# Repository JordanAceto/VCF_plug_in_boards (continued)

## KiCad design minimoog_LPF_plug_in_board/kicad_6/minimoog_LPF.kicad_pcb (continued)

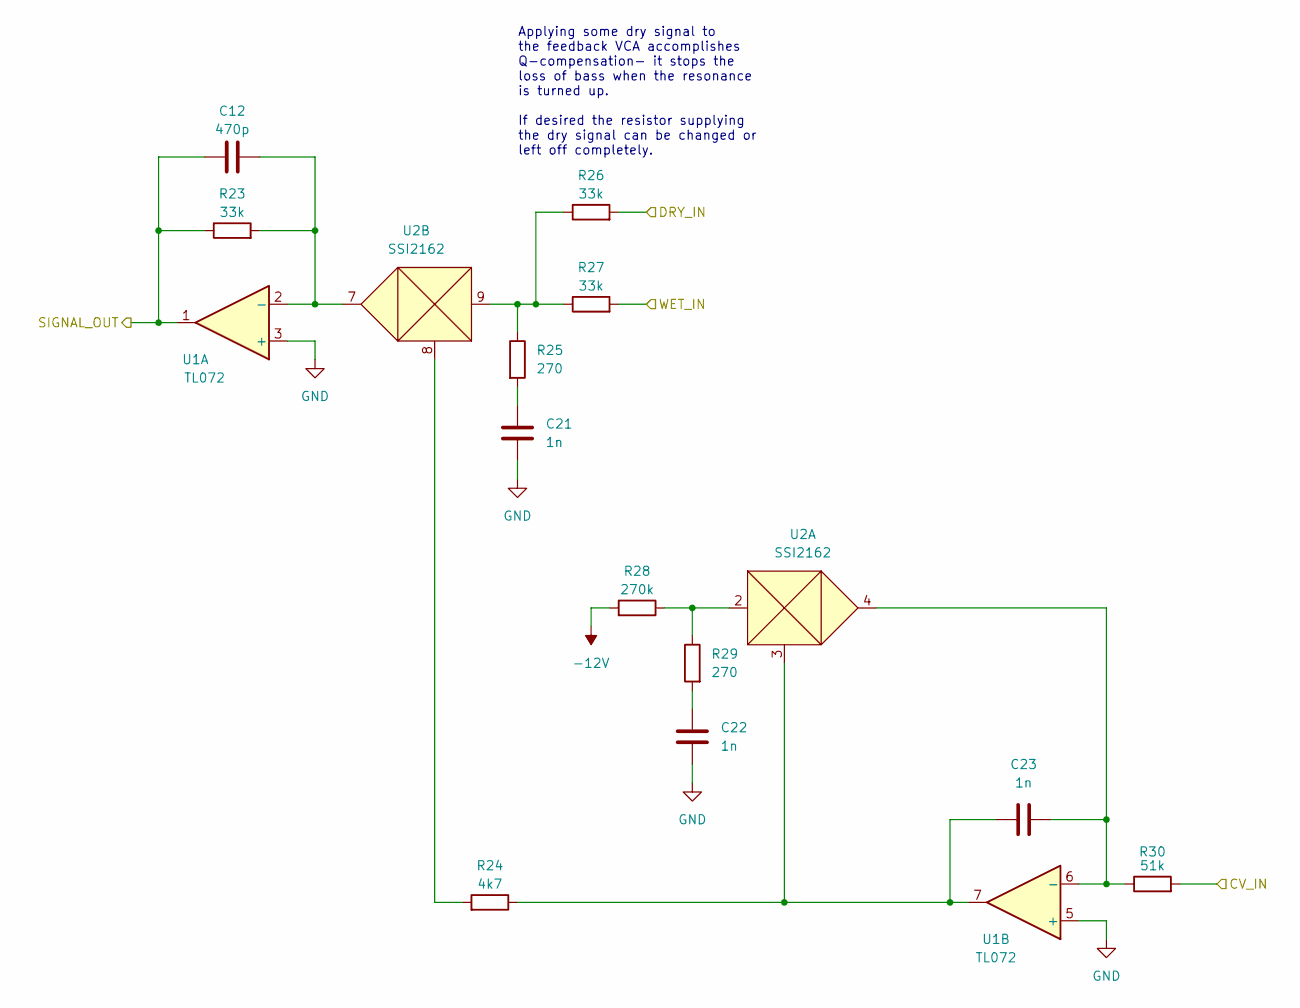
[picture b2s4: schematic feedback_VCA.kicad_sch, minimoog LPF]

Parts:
C12: 470p; C_0603_1608Metric
C21, C22, C23: 1n; C_0603_1608Metric
R23, R26, R27: 33k; R_0603_1608Metric
R24: 4k7; R_0603_1608Metric
R25, R29: 270; R_0603_1608Metric
R28: 270k; R_0603_1608Metric
R30: 51k; R_0603_1608Metric
U1: TL072; SOIC-8_3.9x4.9mm_P1.27mm
U2: SSI2162; SSOP-10_3.9x4.9mm_P1.00mm

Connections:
-12V: R28.2; also elsewhere on the board
/DRY_SIGNAL: R26.2; also elsewhere on the board
/feedback_VCA/CV_IN: R30.2; also elsewhere on the board
/feedback_VCA/SIGNAL_OUT: C12.1, R23.1, U1.1; also elsewhere on the board
/feedback_VCA/WET_IN: R27.2; also elsewhere on the board
GND: C21.2, C22.2, U1.3 (+), U1.5 (+); also elsewhere on the board
unnamed: C12.2, R23.2, U1.2 (-), U2.7
unnamed: C21.1, R25.2
unnamed: C22.1, R29.2
unnamed: C23.1, R24.1, U1.7, U2.3
unnamed: C23.2, R30.1, U1.6 (-), U2.4
unnamed: R24.2, U2.8
unnamed: R25.1, R26.1, R27.1, U2.9
unnamed: R28.1, R29.1, U2.2

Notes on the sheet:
Applying some dry signal to the feedback VCA accomplishes Q-compensation- it stops the loss of bass when the resonance is turned up. If desired the resistor supplying the dry signal can be changed or left off completely.

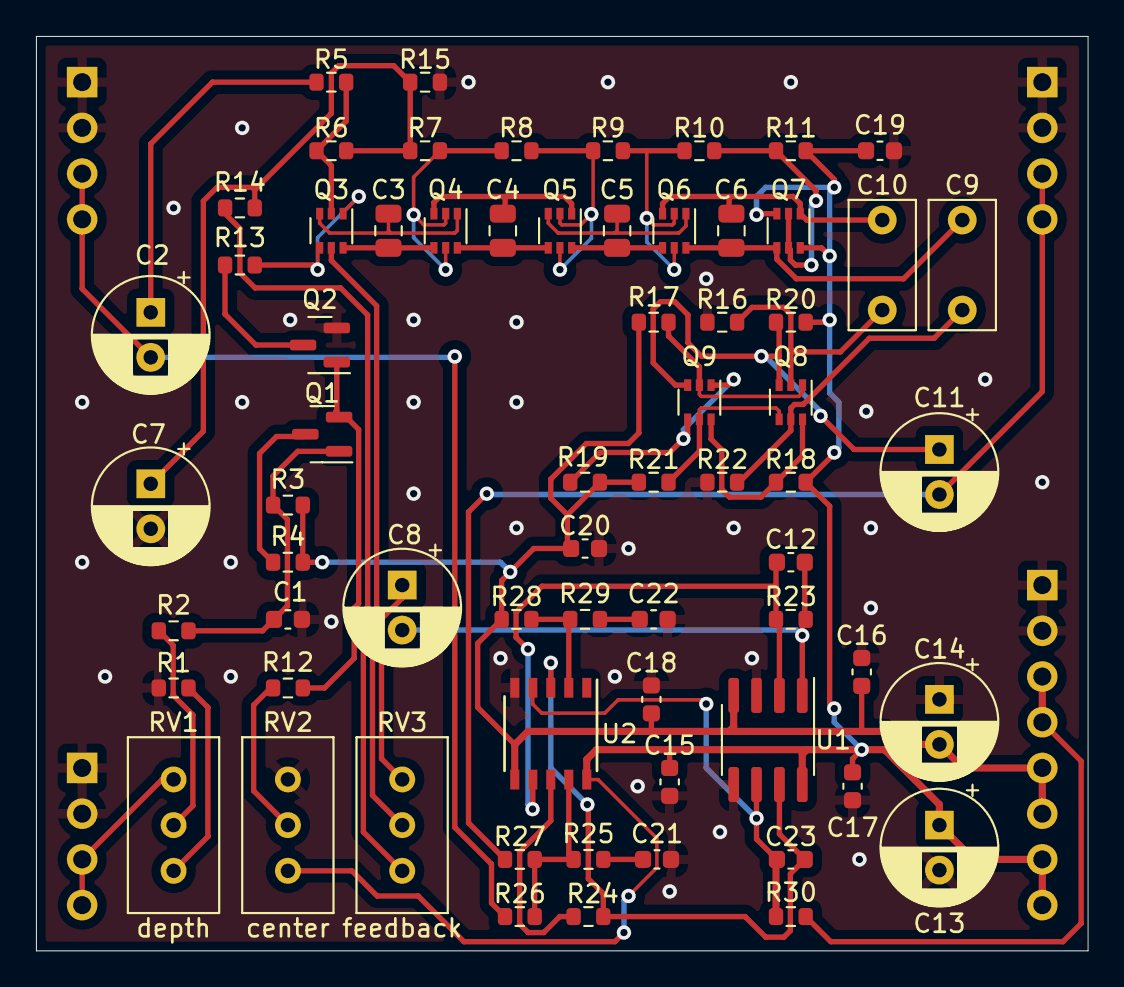
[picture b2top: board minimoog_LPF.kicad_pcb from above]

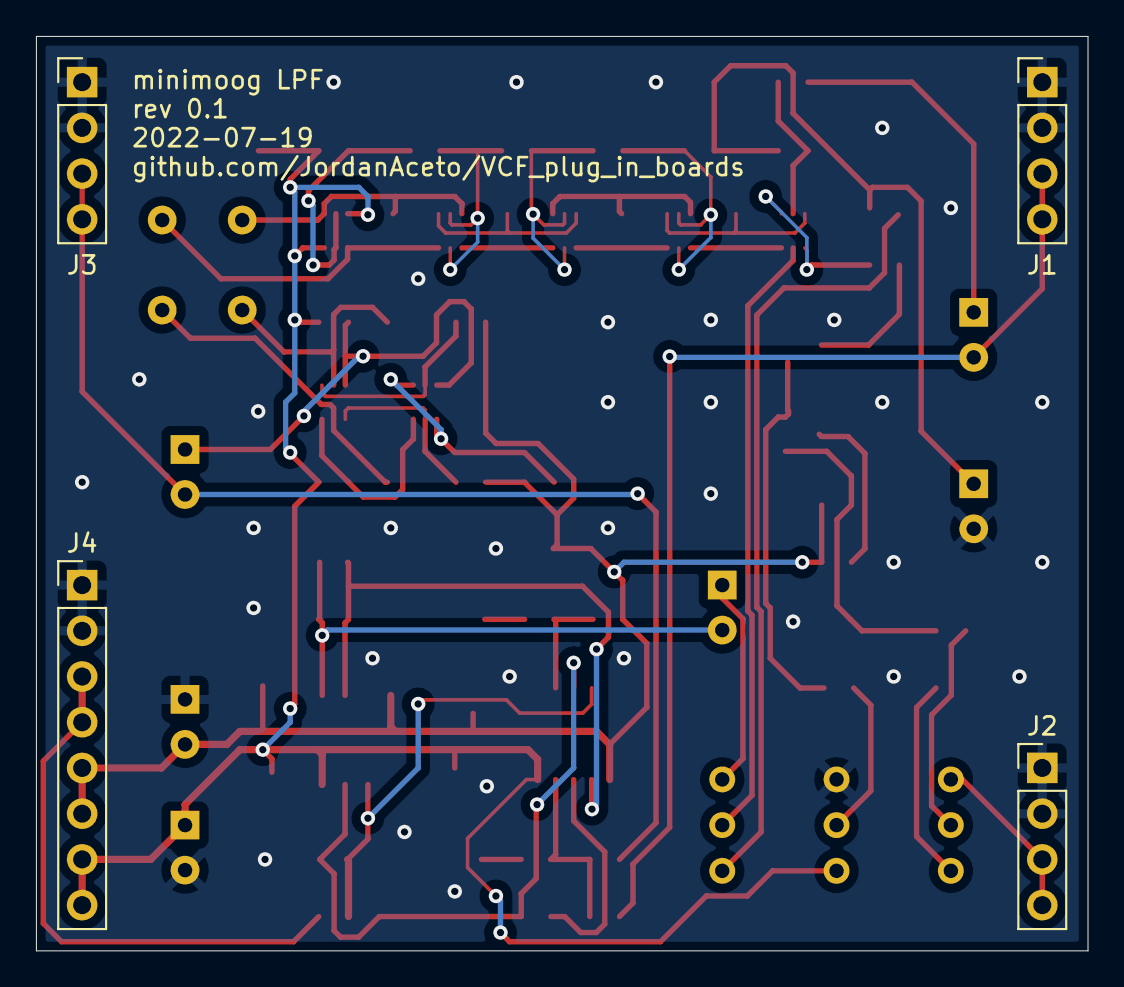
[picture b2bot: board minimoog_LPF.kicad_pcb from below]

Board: 2 copper layers, 58.4 x 50.8 mm, 71 parts (4 on the bottom side), 49 nets.

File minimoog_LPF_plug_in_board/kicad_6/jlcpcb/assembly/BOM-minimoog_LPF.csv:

Comment,Designator,Footprint,LCSC
100nF,"C15,C16,C17,C18,C19,C20",C_0603_1608Metric,C14663
100p,C12,C_0603_1608Metric,C14858
1n,"C1,C21,C22,C23",C_0603_1608Metric,C1588
MMBT3904,Q2,SOT-23,C20526
1k,R2,R_0603_1608Metric,C21190
1k2,"R18,R19,R20",R_0603_1608Metric,C22765
150,"R10,R7,R8,R9",R_0603_1608Metric,C22808
220k,"R17,R21,R3",R_0603_1608Metric,C22961
220,"R1,R11,R15",R_0603_1608Metric,C22962
270k,R28,R_0603_1608Metric,C22965
270,"R25,R29",R_0603_1608Metric,C22966
330,"R14,R4,R6",R_0603_1608Metric,C23138
4k7,R24,R_0603_1608Metric,C23162
51k,R30,R_0603_1608Metric,C23196
680,R13,R_0603_1608Metric,C23228
100k,R12,R_0603_1608Metric,C25803
47k,"R16,R22",R_0603_1608Metric,C25819
BCM847,"Q3,Q4,Q5,Q6,Q7,Q8,Q9",SOT-363_SC-70-6,C396099
33k,"R23,R26,R27,R5",R_0603_1608Metric,C4216
TL072,U1,SOIC-8_3.9x4.9mm_P1.27mm,C6961
MMBT3906,Q1,SOT-23,

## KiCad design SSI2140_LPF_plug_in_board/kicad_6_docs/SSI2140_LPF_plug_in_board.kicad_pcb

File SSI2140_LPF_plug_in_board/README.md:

## SSI2140 4-pole Low Pass Filter plug-in board

Small SSI2140 based low pass filter PCB, designed to plug into a larger motherboard.

## Details

Basic datasheet implementation of the SSI2140 lowpass filter with "Output Gain" Q Compensation.

## Inputs

-Audio in: dry audio input to be filtered.

-Frequency CV in: 0 volts to +2.048 volts, higher voltage = higher sweep.

-Feedback CV in: 0 volts to +2.048 volts, higher voltage = more feedback.

## Outputs

-Audio out: filtered audio output.

## Power Supply Requirements

A bipolar 12 volt power supply is required. This will typically come from the motherboard.

## Calibration

-RV1 (depth trim): trims the depth of incoming frequency CV signals. Turn CW for greater depth and CCW for less depth. Adjust to taste.

-RV2 (center trim): trims the center frequency of the filter. Turn CW for higher center frequency and CCW for lower center frequency. Adjust to taste.

-RV3 (feedback trim): trims the maximum amount of feedback. Turn CW for more maximum feedback and CCW for less maximum feedback. Exercise caution when adjusting this, as extreme settings can result in loud oscillations which could damage your ears or speakers if you are monitoring the sound with a loud amplifier. If you set this trimmer to be right on the edge of oscillation when about +2 volts is applied to the feedback CV input then make sure to sweep the frequency through its entire range, as a setting that doesn't squeal at certain frequency settings may squeal at other settings.

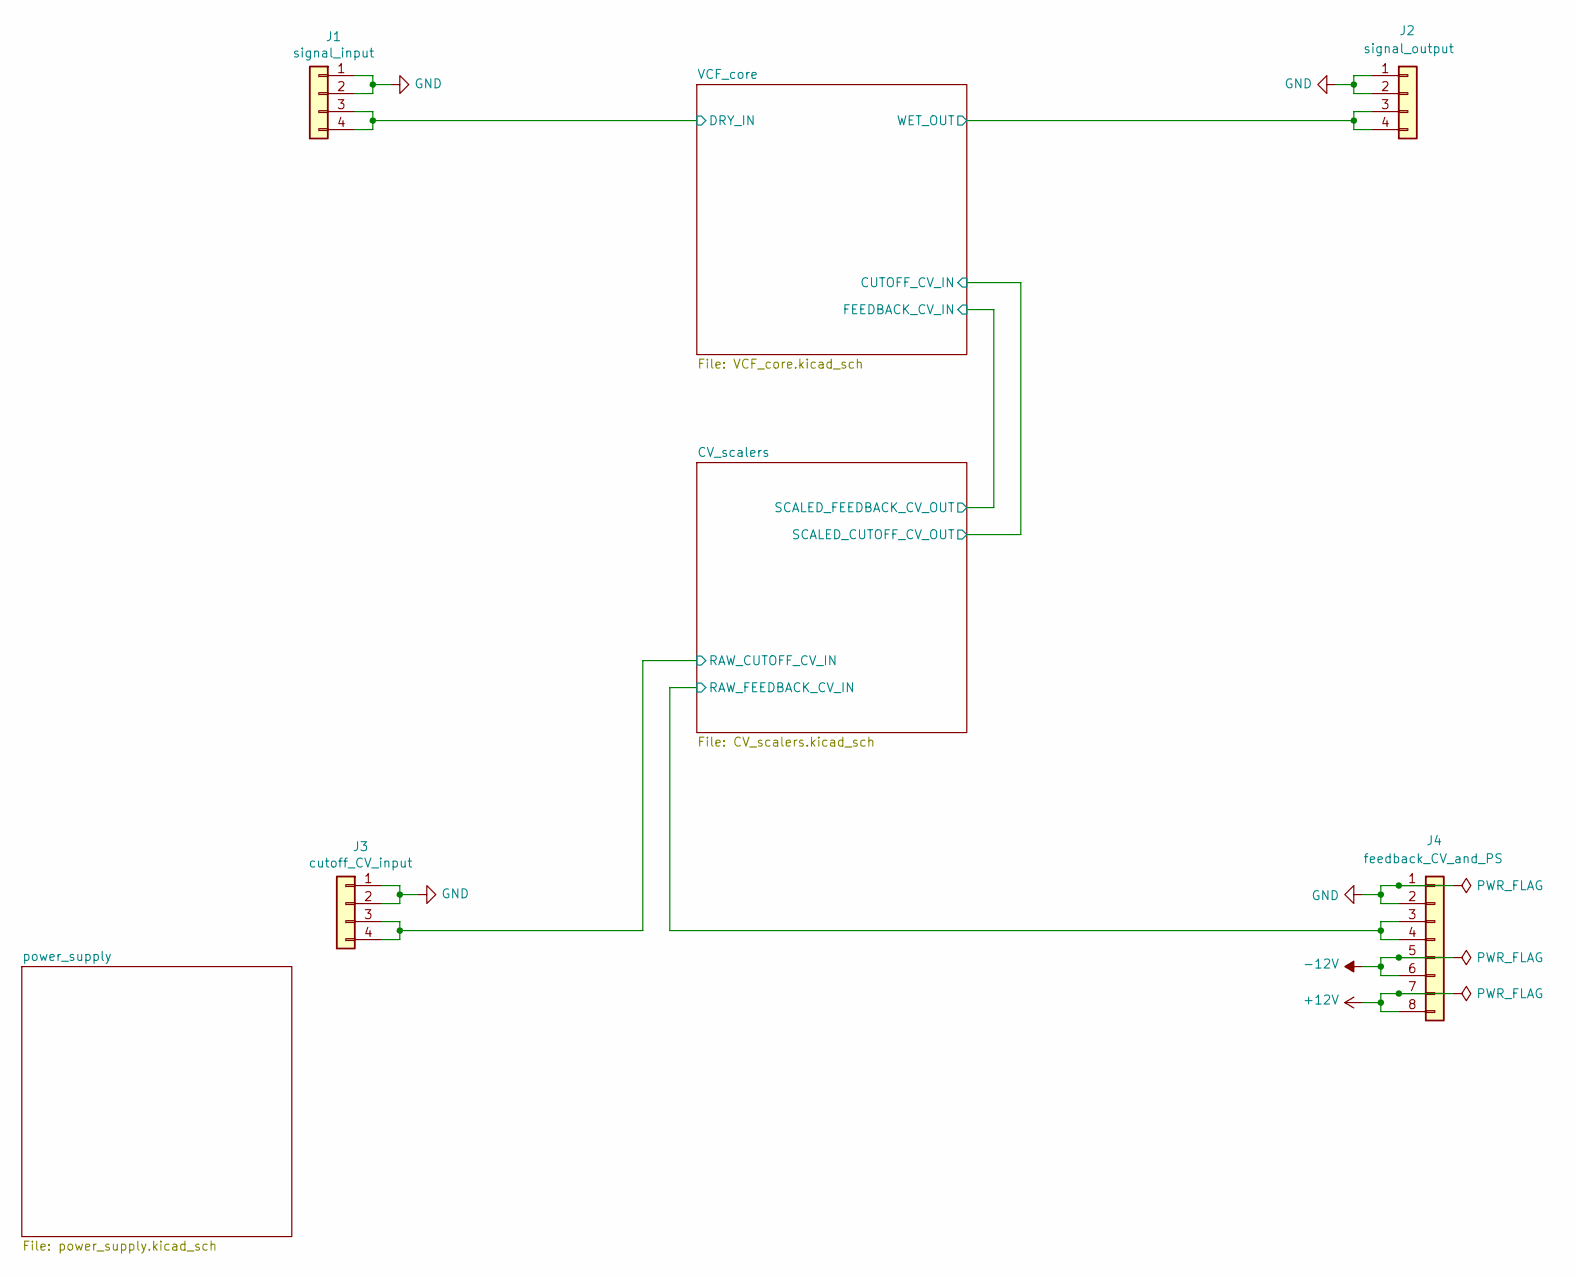
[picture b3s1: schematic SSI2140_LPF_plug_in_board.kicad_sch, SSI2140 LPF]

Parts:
J1: signal_input; PinHeader_1x04_P2.54mm_Vertical
J2: signal_output; PinHeader_1x04_P2.54mm_Vertical
J3: cutoff_CV_input; PinHeader_1x04_P2.54mm_Vertical
J4: feedback_CV_and_PS; PinHeader_1x08_P2.54mm_Vertical

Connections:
+12V: J4.7, J4.8; also elsewhere on the board
-12V: J4.5, J4.6; also elsewhere on the board
/CV_scalers/RAW_CUTOFF_CV_IN: J3.3, J3.4; also elsewhere on the board
/CV_scalers/RAW_FEEDBACK_CV_IN: J4.3, J4.4; also elsewhere on the board
/VCF_core/DRY_IN: J1.3, J1.4; also elsewhere on the board
/VCF_core/WET_OUT: J2.3, J2.4; also elsewhere on the board
GND: J1.1, J1.2, J2.1, J2.2, J3.1, J3.2, J4.1, J4.2; also elsewhere on the board

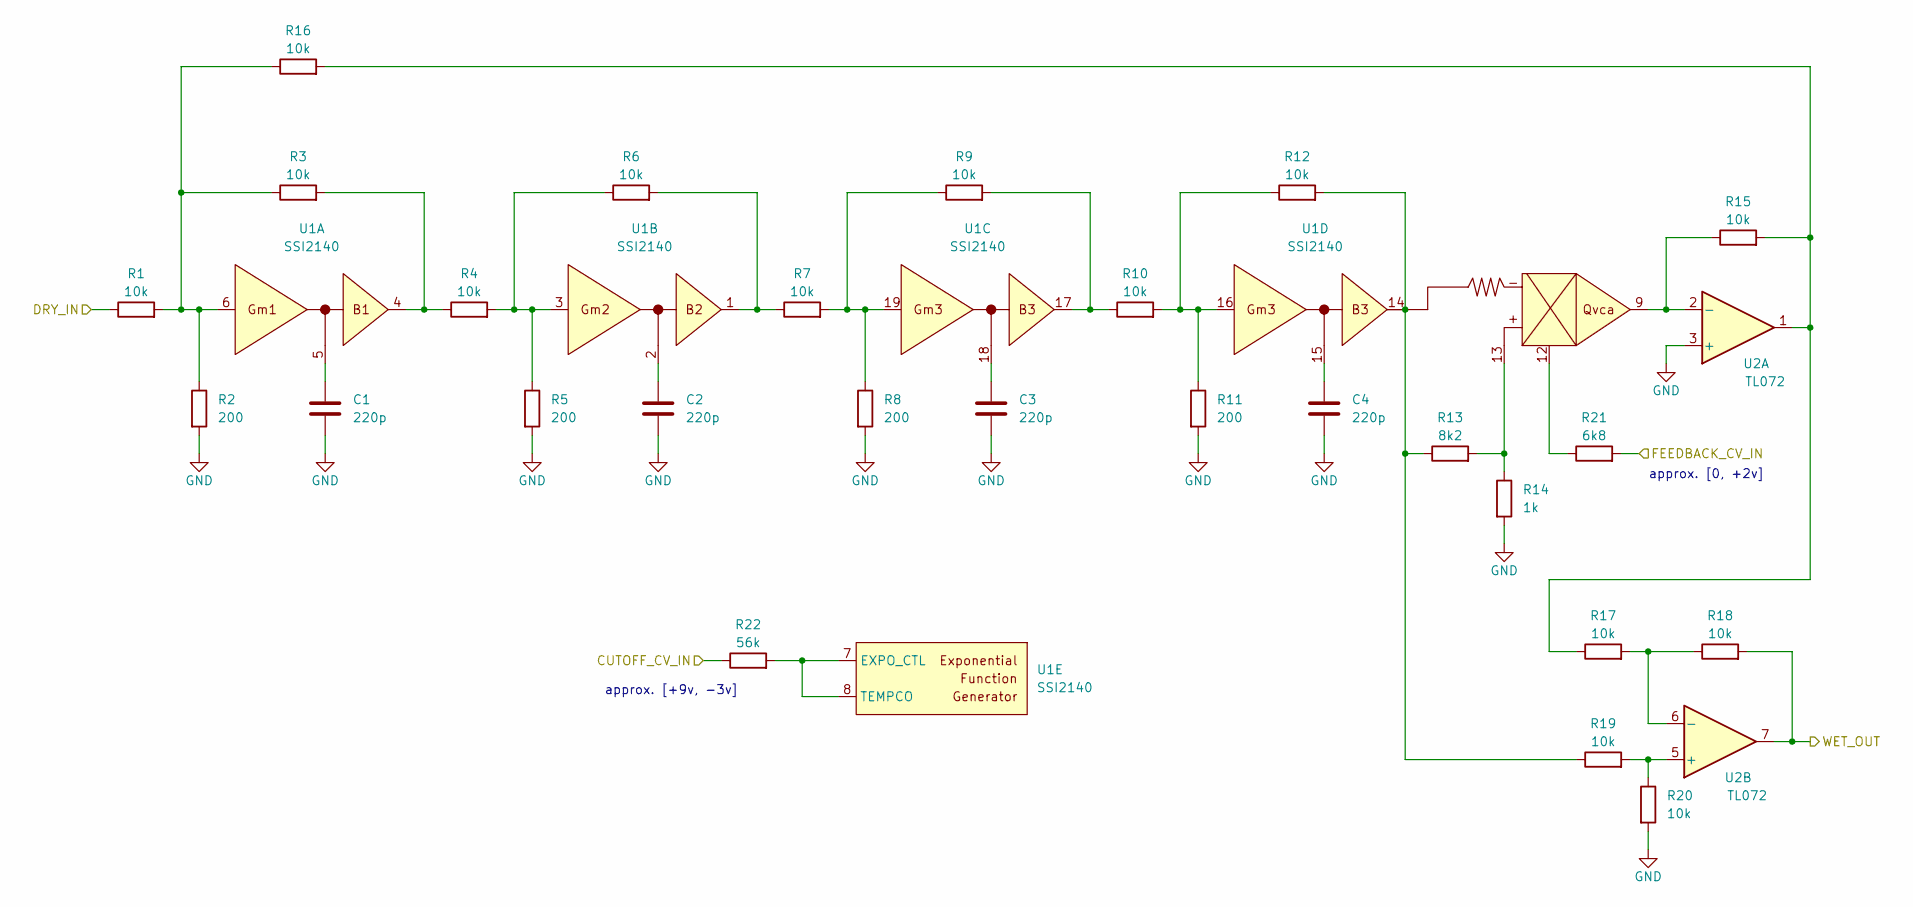
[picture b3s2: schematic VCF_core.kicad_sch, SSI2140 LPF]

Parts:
C1, C2, C3, C4: 220p; timing_cap_dual_fp
R1, R3, R4, R6, R7, R9, R10, R12, R15, R16, R17, R18, R19, R20: 10k; R_0805_2012Metric
R2, R5, R8, R11: 200; R_0805_2012Metric
R13: 8k2; R_0805_2012Metric
R14: 1k; R_0805_2012Metric
R21: 6k8; R_0805_2012Metric
R22: 56k; R_0805_2012Metric
U1: SSI2140; TSSOP-20_4.4x6.5mm_P0.65mm
U2: TL072; SOIC-8_3.9x4.9mm_P1.27mm

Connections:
/CV_scalers/SCALED_CUTOFF_CV_OUT: R22.1; also elsewhere on the board
/CV_scalers/SCALED_FEEDBACK_CV_OUT: R21.2; also elsewhere on the board
/VCF_core/DRY_IN: R1.1; also elsewhere on the board
/VCF_core/WET_OUT: R18.2, U2.7; also elsewhere on the board
GND: C1.2, C2.2, C3.2, C4.2, R2.2, R5.2, R8.2, R11.2, R14.2, R20.2, U2.3 (+); also elsewhere on the board
unnamed: C1.1, U1.5
unnamed: C2.1, U1.2
unnamed: C3.1, U1.18
unnamed: C4.1, U1.15
unnamed: R3.2, R4.1, U1.4
unnamed: R4.2, R5.1, R6.1, U1.3
unnamed: R6.2, R7.1, U1.1
unnamed: R7.2, R8.1, R9.1, U1.19
unnamed: R9.2, R10.1, U1.17
unnamed: R10.2, R11.1, R12.1, U1.16
unnamed: R12.2, R13.1, R19.1, U1.14
unnamed: R13.2, R14.1, U1.13
unnamed: R15.1, U1.9, U2.2 (-)
unnamed: R1.2, R2.1, R3.1, R16.1, U1.6
unnamed: R15.2, R16.2, R17.1, U2.1
unnamed: R17.2, R18.1, U2.6 (-)
unnamed: R19.2, R20.1, U2.5 (+)
unnamed: R21.1, U1.12
unnamed: R22.2, U1.7 (EXPO_CTL), U1.8 (TEMPCO)

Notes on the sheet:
approx. [0, +2v]
approx. [+9v, -3v]

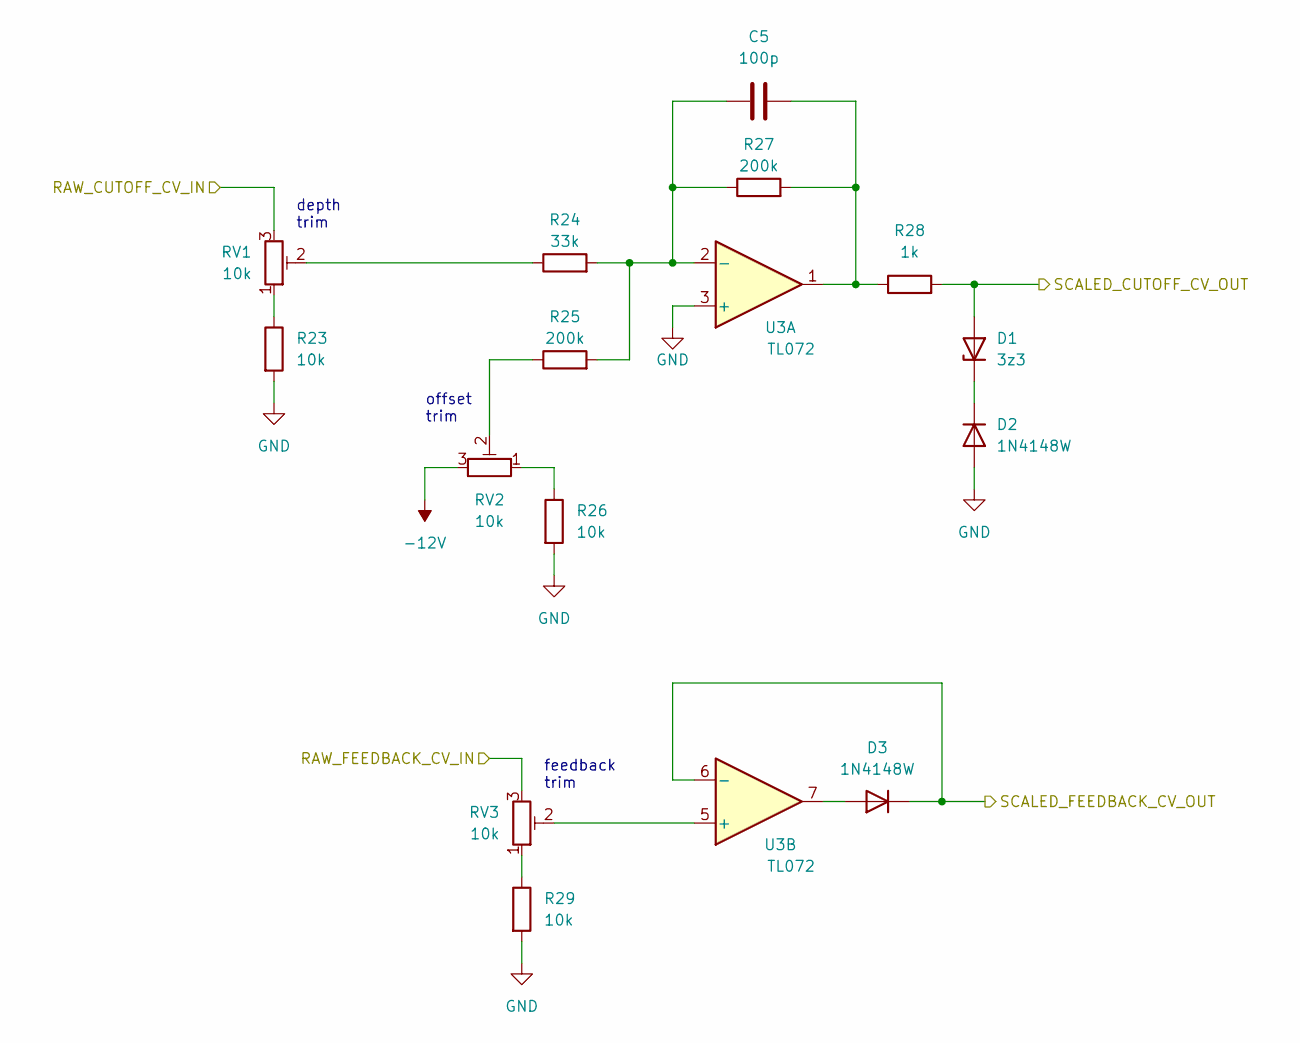
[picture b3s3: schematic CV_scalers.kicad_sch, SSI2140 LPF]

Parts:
C5: 100p; C_0805_2012Metric
D1: 3z3; D_SOD-123
D2, D3: 1N4148W; D_SOD-123
R23, R26, R29: 10k; R_0805_2012Metric
R24: 33k; R_0805_2012Metric
R25, R27: 200k; R_0805_2012Metric
R28: 1k; R_0805_2012Metric
RV1, RV2, RV3: 10k; Potentiometer_Bourns_3296W_Vertical
U3: TL072; SOIC-8_3.9x4.9mm_P1.27mm

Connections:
-12V: RV2.3; also elsewhere on the board
/CV_scalers/RAW_CUTOFF_CV_IN: RV1.3; also elsewhere on the board
/CV_scalers/RAW_FEEDBACK_CV_IN: RV3.3; also elsewhere on the board
/CV_scalers/SCALED_CUTOFF_CV_OUT: D1.2 (A), R28.2; also elsewhere on the board
/CV_scalers/SCALED_FEEDBACK_CV_OUT: D3.1 (K), U3.6 (-); also elsewhere on the board
GND: D2.2 (A), R23.2, R26.2, R29.2, U3.3 (+); also elsewhere on the board
unnamed: C5.1, R24.2, R25.2, R27.1, U3.2 (-)
unnamed: C5.2, R27.2, R28.1, U3.1
unnamed: D1.1 (K), D2.1 (K)
unnamed: D3.2 (A), U3.7
unnamed: R23.1, RV1.1
unnamed: R24.1, RV1.2
unnamed: R25.1, RV2.2
unnamed: R26.1, RV2.1
unnamed: R29.1, RV3.1
unnamed: RV3.2, U3.5 (+)

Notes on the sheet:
offset trim
depth trim
feedback trim

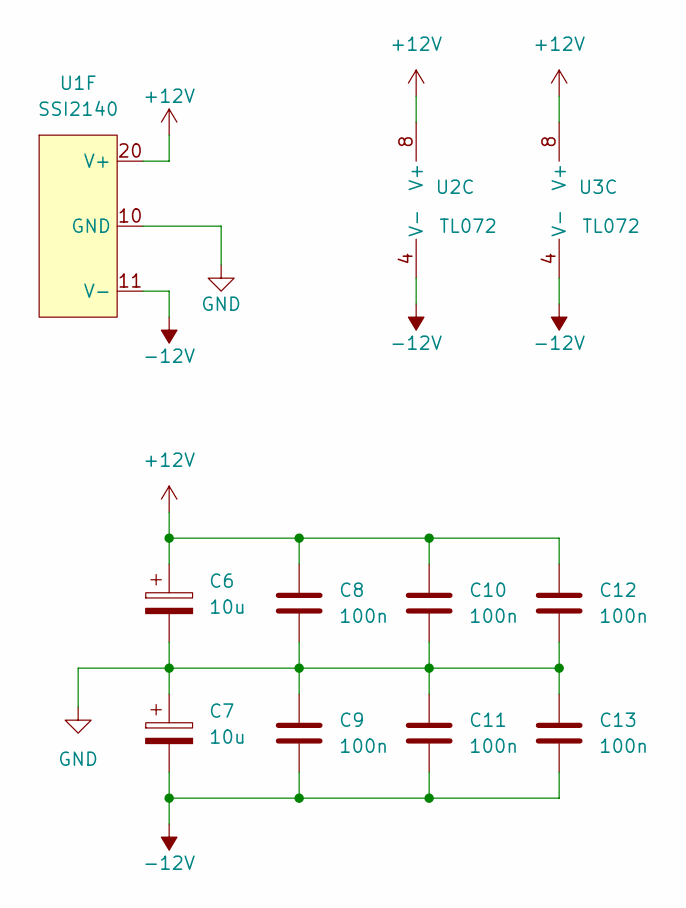
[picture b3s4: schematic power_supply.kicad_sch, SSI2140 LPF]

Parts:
C6, C7: 10u; CP_Radial_D6.3mm_P2.50mm
C8, C9, C10, C11, C12, C13: 100n; C_0805_2012Metric
U1: SSI2140; TSSOP-20_4.4x6.5mm_P0.65mm
U2, U3: TL072; SOIC-8_3.9x4.9mm_P1.27mm

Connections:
+12V: C6.1, C8.1, C10.1, C12.1, U1.20 (V+), U2.8 (V+), U3.8 (V+); also elsewhere on the board
-12V: C7.2, C9.2, C11.2, C13.2, U1.11 (V-), U2.4 (V-), U3.4 (V-); also elsewhere on the board
GND: C6.2, C7.1, C8.2, C9.1, C10.2, C11.1, C12.2, C13.1, U1.10 (GND); also elsewhere on the board

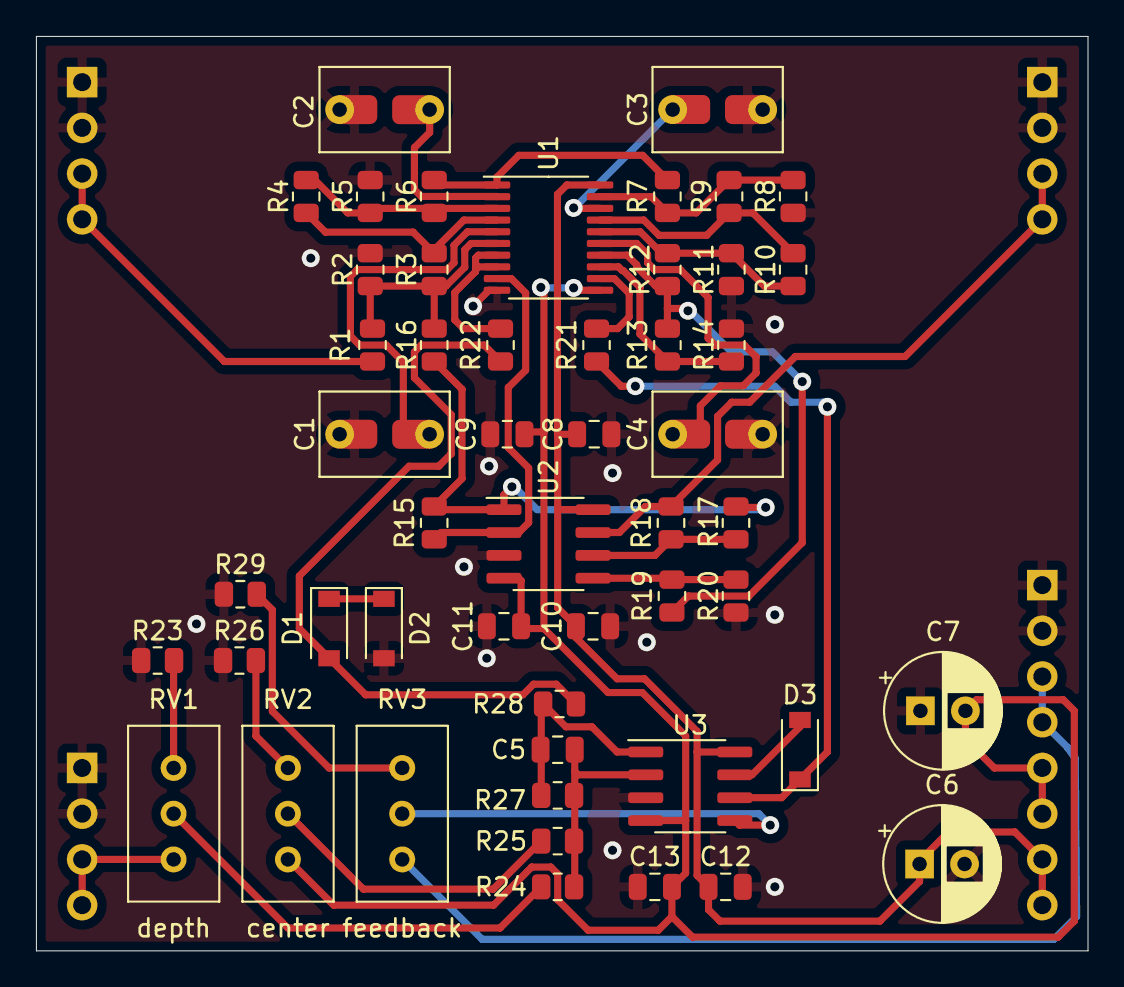
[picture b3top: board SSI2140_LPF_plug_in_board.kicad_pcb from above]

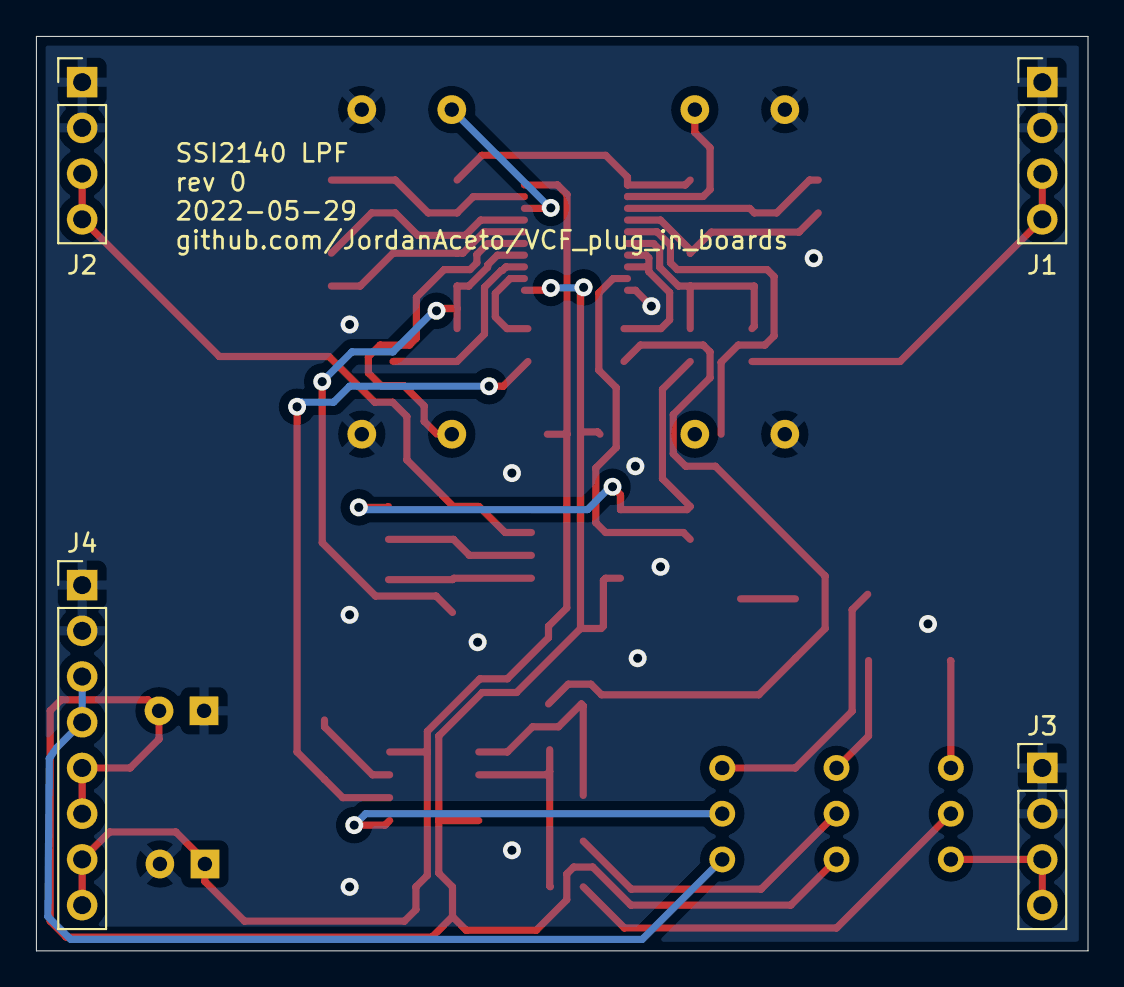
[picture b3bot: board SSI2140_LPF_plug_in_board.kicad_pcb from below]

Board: 2 copper layers, 58.4 x 50.8 mm, 55 parts (4 on the bottom side), 38 nets.

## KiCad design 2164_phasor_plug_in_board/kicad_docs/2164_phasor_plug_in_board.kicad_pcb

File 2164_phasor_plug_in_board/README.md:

# 2164 Phasor Plug-In Board

Small 6 stage SSM2164 based phase shifter PCB, designed to plug into a larger motherboard.

## Details

Six stage phase shifter implemented with SSI2164 quad VCAs.

Voltage controlled feedback is provided, consistent with the other filter plug-in boards.

Construction documents for the low cost pcb assembly service from JLCPCB are included. A few parts are not included in the assembly documents, such as the through hole components, the SSI2164 chips, and also the 220pf timing capacitors for the filter stages. These are left to the builder to install. These should be good quality C0G/NP0 0805 capacitors with 2% or better tolerance.

## Inputs

-Audio in: dry audio input to be phase shifted.

-Frequency CV in: 0 volts to +2.048 volts, higher voltage = higher sweep.

-Feedback CV in: 0 volts to +2.048 volts, higher voltage = more feedback.

## Outputs

-Audio out: phase shifted audio output.

## Power Supply Requirements

A bipolar 12 volt power supply is needed. This will typically come from the motherboard.

## Calibration

- See the top level README for calibration instructions.

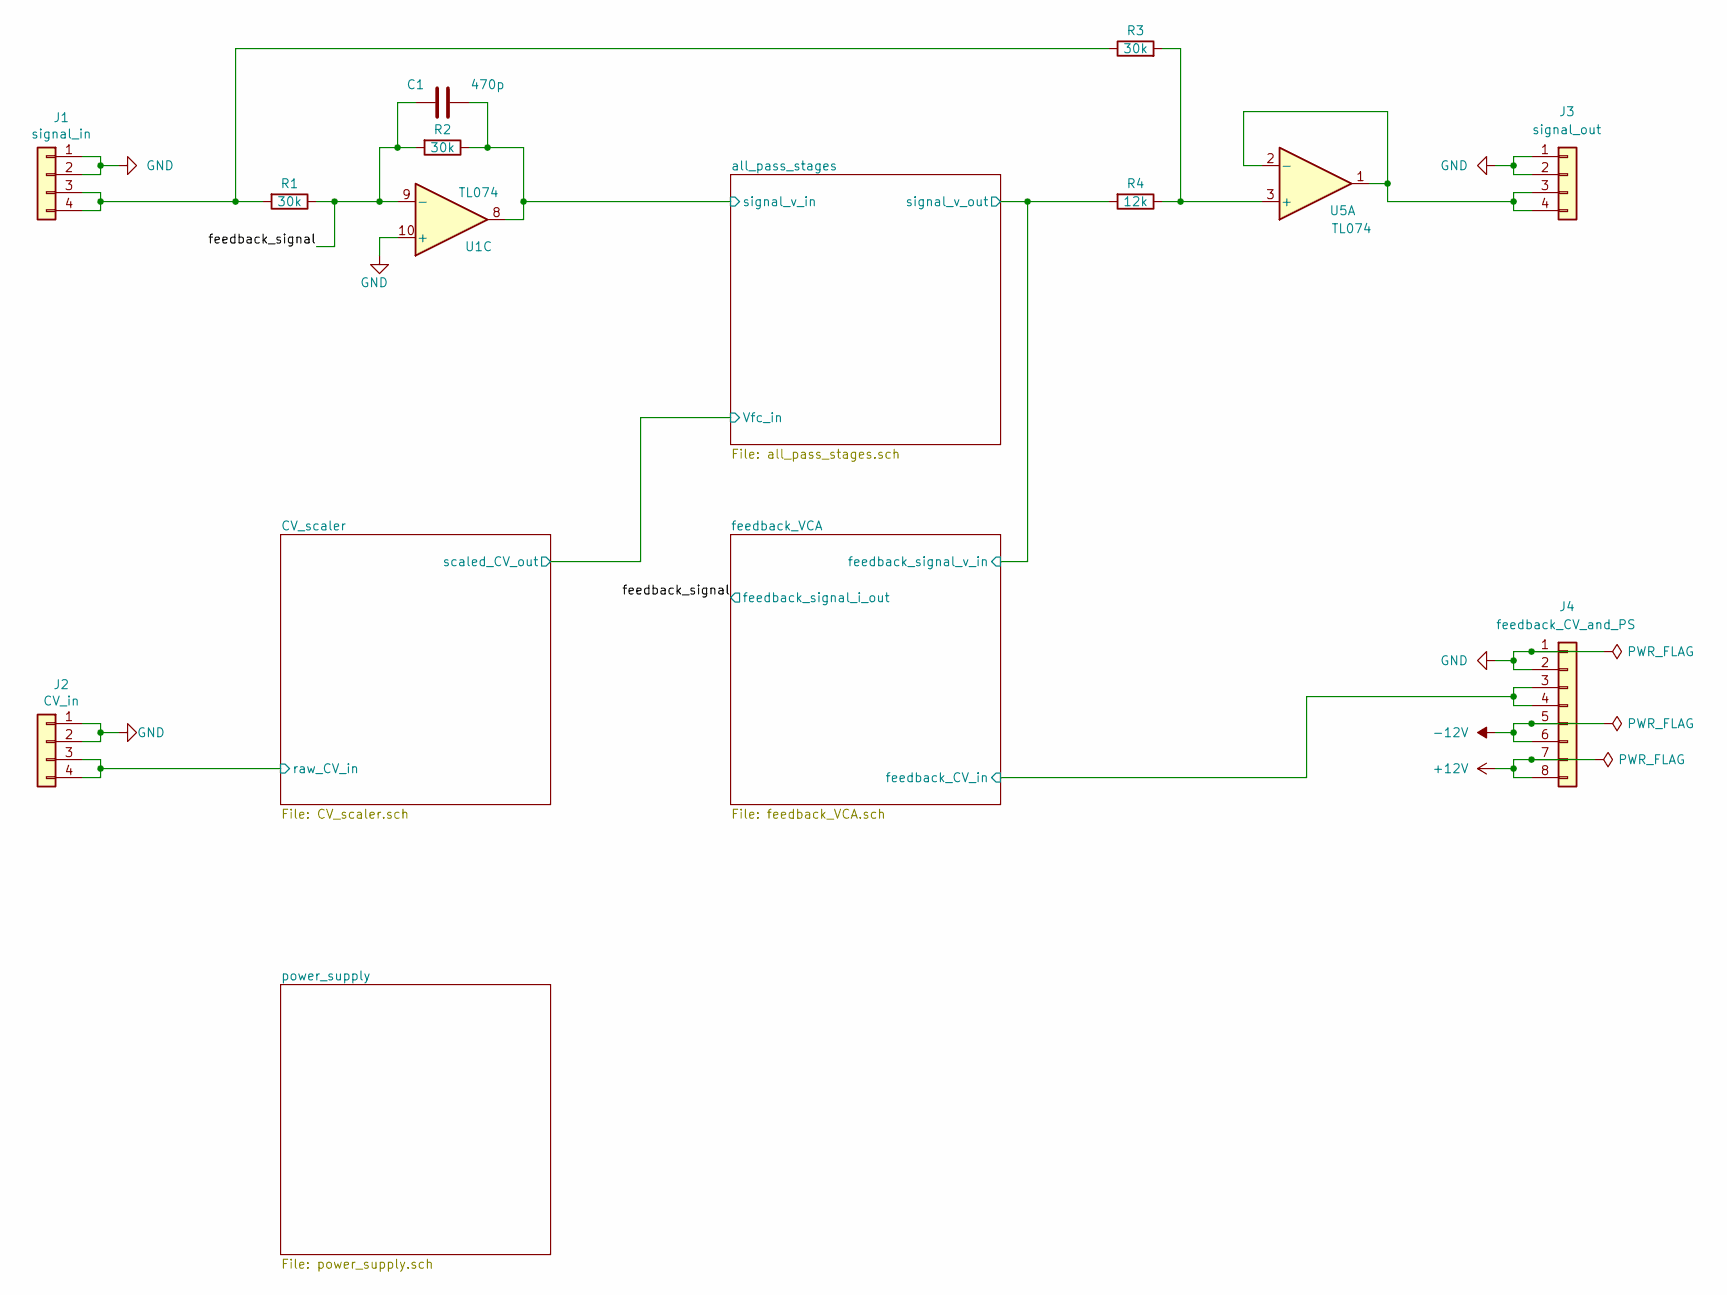
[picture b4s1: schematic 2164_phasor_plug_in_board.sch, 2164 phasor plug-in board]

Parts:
C1: 470p; C_0603_1608Metric
J1: signal_in; PinHeader_1x04_P2.54mm_Vertical
J2: CV_in; PinHeader_1x04_P2.54mm_Vertical
J3: signal_out; PinHeader_1x04_P2.54mm_Vertical
J4: feedback_CV_and_PS; PinHeader_1x08_P2.54mm_Vertical
R1, R2, R3: 30k; R_0603_1608Metric
R4: 12k; R_0603_1608Metric
U1, U5: TL074; TSSOP-14_4.4x5mm_P0.65mm

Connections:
+12V: J4.7, J4.8; also elsewhere on the board
-12V: J4.5, J4.6; also elsewhere on the board
/CV_scaler/raw_CV_in: J2.3, J2.4; also elsewhere on the board
/all_pass_stages/signal_v_in: C1.1, R2.1, U1.8; also elsewhere on the board
/feedback_VCA/feedback_CV_in: J4.3, J4.4; also elsewhere on the board
/feedback_VCA/feedback_signal_v_in: R4.2; also elsewhere on the board
/feedback_signal: C1.2, R1.1, R2.2, U1.9 (-); also elsewhere on the board
GND: J1.1, J1.2, J2.1, J2.2, J3.1, J3.2, J4.1, J4.2, U1.10 (+); also elsewhere on the board
unnamed: J1.3, J1.4, R1.2, R3.1
unnamed: J3.3, J3.4, U5.1, U5.2 (-)
unnamed: R3.2, R4.1, U5.3 (+)

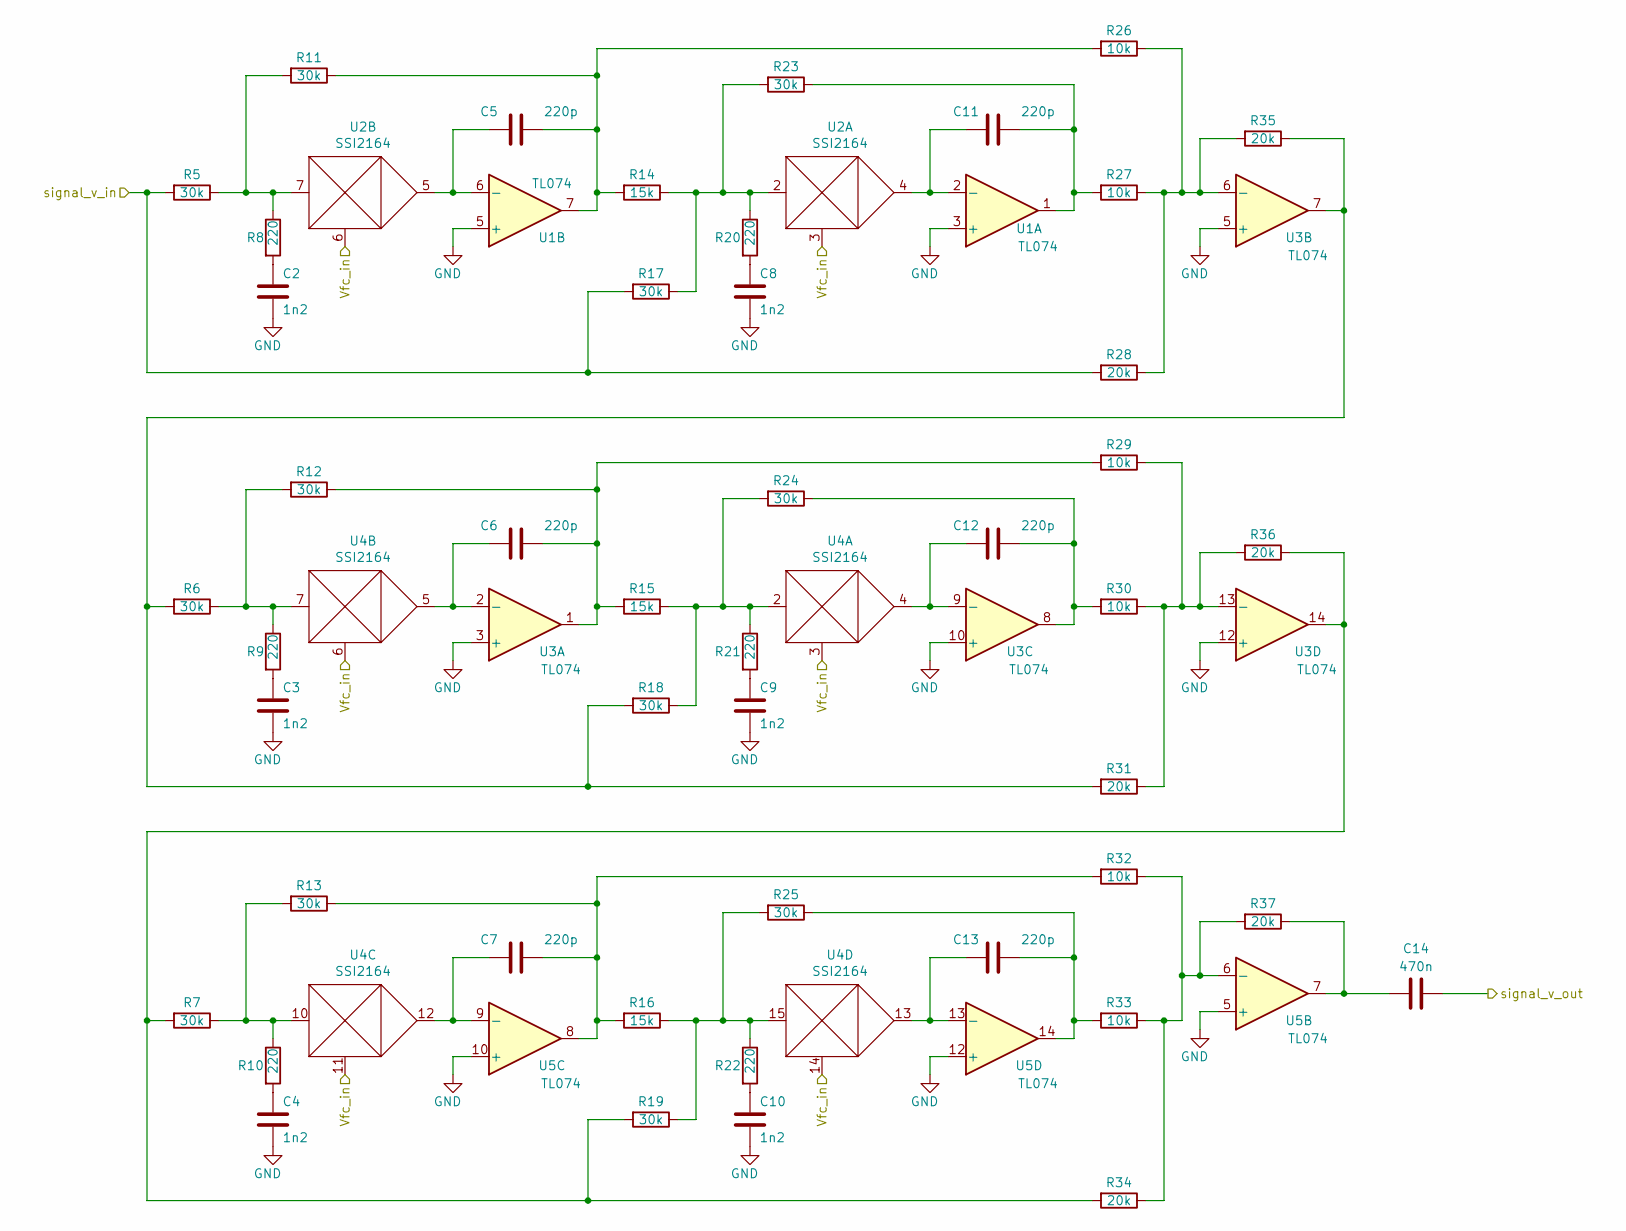
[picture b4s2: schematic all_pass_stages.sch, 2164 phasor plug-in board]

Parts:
C2, C3, C4, C8, C9, C10: 1n2; C_0603_1608Metric
C5, C6, C7, C11, C12, C13: 220p; C_0805_2012Metric
C14: 470n; C_Rect_L7.2mm_W3.5mm_P5.00mm_FKS2_FKP2_MKS2_MKP2
R5, R6, R7, R11, R12, R13, R17, R18, R19, R23, R24, R25: 30k; R_0603_1608Metric
R8, R9, R10, R20, R21, R22: 220; R_0603_1608Metric
R14, R15, R16: 15k; R_0603_1608Metric
R26, R27, R29, R30, R32, R33: 10k; R_0603_1608Metric
R28, R31, R34, R35, R36, R37: 20k; R_0603_1608Metric
U1, U3, U5: TL074; TSSOP-14_4.4x5mm_P0.65mm
U2, U4: SSI2164; SOIC-16_3.9x9.9mm_P1.27mm

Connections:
/all_pass_stages/Vfc_in: U2.3, U2.6, U4.3, U4.6, U4.11, U4.14; also elsewhere on the board
/all_pass_stages/signal_v_in: R5.2, R17.2, R28.2; also elsewhere on the board
/feedback_VCA/feedback_signal_v_in: C14.1; also elsewhere on the board
GND: C2.2, C3.2, C4.2, C8.2, C9.2, C10.2, U1.3 (+), U1.5 (+), U3.3 (+), U3.5 (+), U3.10 (+), U3.12 (+), U5.5 (+), U5.10 (+), U5.12 (+); also elsewhere on the board
unnamed: C2.1, R8.2
unnamed: C3.1, R9.2
unnamed: C4.1, R10.2
unnamed: C5.1, R11.1, R14.2, R26.2, U1.7
unnamed: C5.2, U1.6 (-), U2.5
unnamed: C6.1, R12.1, R15.2, R29.2, U3.1
unnamed: C6.2, U3.2 (-), U4.5
unnamed: C7.1, R13.1, R16.2, R32.2, U5.8
unnamed: C7.2, U4.12, U5.9 (-)
unnamed: C8.1, R20.2
unnamed: C9.1, R21.2
unnamed: C10.1, R22.2
unnamed: C11.1, R23.1, R27.2, U1.1
unnamed: C11.2, U1.2 (-), U2.4
unnamed: C12.1, R24.1, R30.2, U3.8
unnamed: C12.2, U3.9 (-), U4.4
unnamed: C13.1, R25.1, R33.2, U5.14
unnamed: C13.2, U4.13, U5.13 (-)
unnamed: C14.2, R37.1, U5.7
unnamed: R7.1, R10.1, R13.2, U4.10
unnamed: R5.1, R8.1, R11.2, U2.7
unnamed: R6.1, R9.1, R12.2, U4.7
unnamed: R14.1, R17.1, R20.1, R23.2, U2.2
unnamed: R15.1, R18.1, R21.1, R24.2, U4.2
unnamed: R16.1, R19.1, R22.1, R25.2, U4.15
unnamed: R6.2, R18.2, R31.2, R35.1, U3.7
unnamed: R7.2, R19.2, R34.2, R36.1, U3.14
unnamed: R26.1, R27.1, R28.1, R35.2, U3.6 (-)
unnamed: R29.1, R30.1, R31.1, R36.2, U3.13 (-)
unnamed: R32.1, R33.1, R34.1, R37.2, U5.6 (-)
